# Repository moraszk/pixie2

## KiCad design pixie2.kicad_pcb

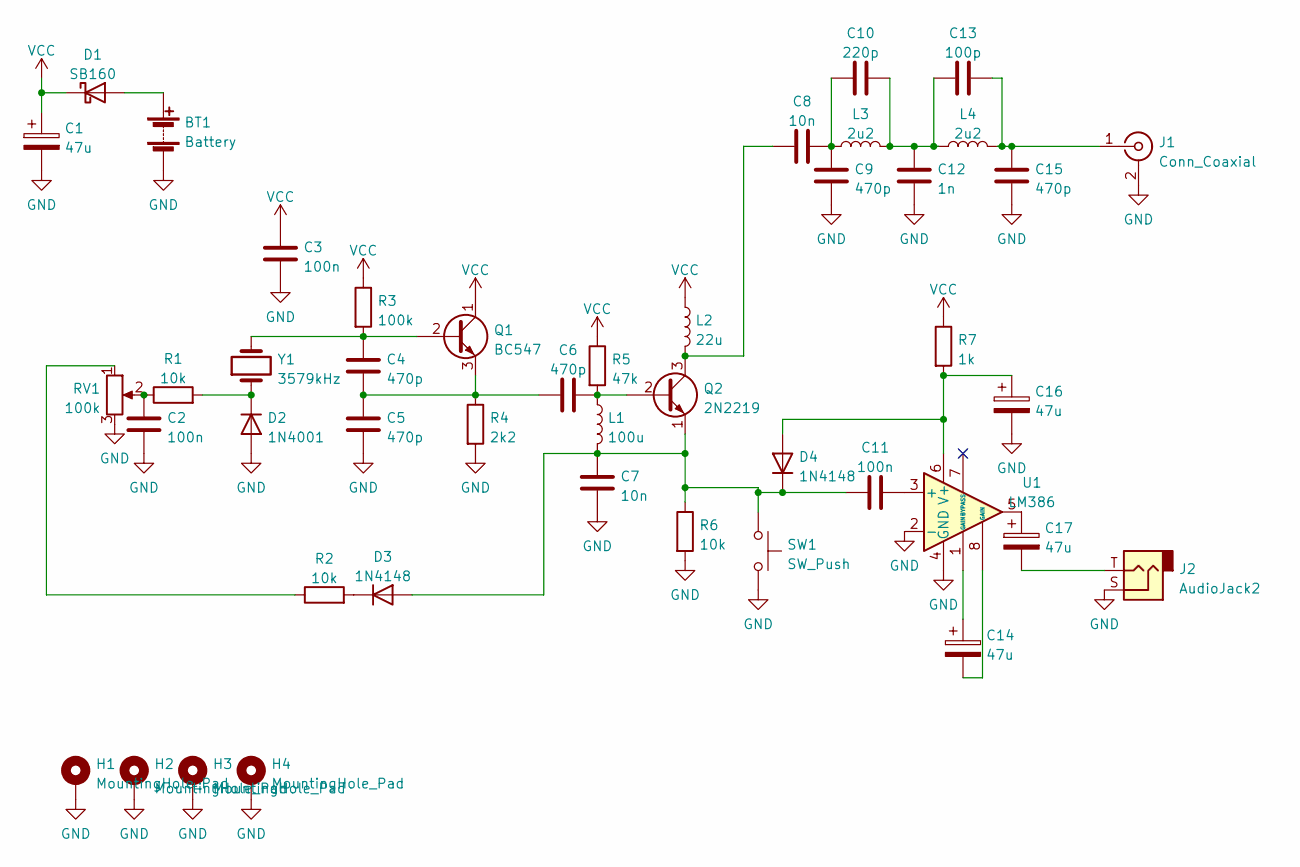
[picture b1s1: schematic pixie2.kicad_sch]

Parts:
BT1: Battery; BarrelJack_GCT_DCJ200-10-A_Horizontal
C1, C14, C16, C17: 47u; CP_Radial_D5.0mm_P2.00mm
C2, C3, C11: 100n; C_Disc_D5.0mm_W2.5mm_P2.50mm
C4, C5, C6, C9, C15: 470p; C_Disc_D3.8mm_W2.6mm_P2.50mm
C7, C8: 10n; C_Disc_D3.8mm_W2.6mm_P2.50mm
C10: 220p; C_Disc_D5.0mm_W2.5mm_P2.50mm
C12: 1n; C_Rect_L4.0mm_W2.5mm_P2.50mm
C13: 100p; C_Disc_D5.0mm_W2.5mm_P2.50mm
D1: SB160; D_DO-41_SOD81_P5.08mm_Vertical_KathodeUp
D2: 1N4001; D_DO-41_SOD81_P5.08mm_Vertical_KathodeUp
D3: 1N4148; D_DO-35_SOD27_P2.54mm_Vertical_KathodeUp
D4: 1N4148; D_DO-35_SOD27_P7.62mm_Horizontal
H1, H2, H3, H4: MountingHole_Pad; MountingHole_3.2mm_M3_Pad
J1: Conn_Coaxial; MountingHole_4.3mm_M4_Pad
J2: AudioJack2; Jack_3.5mm_Ledino_KB3SPRS_Horizontal
L1: 100u; L_Axial_L7.0mm_D3.3mm_P5.08mm_Vertical_Fastron_MICC
L2: 22u; L_Axial_L7.0mm_D3.3mm_P10.16mm_Horizontal_Fastron_MICC
L3: 2u2; L_Axial_L7.0mm_D3.3mm_P10.16mm_Horizontal_Fastron_MICC
L4: 2u2; L_Axial_L7.0mm_D3.3mm_P5.08mm_Vertical_Fastron_MICC
Q1: BC547; TO-92_Inline
Q2: 2N2219; TO-39-3
R1: 10k; R_Axial_DIN0204_L3.6mm_D1.6mm_P2.54mm_Vertical
R2, R6: 10k; R_Axial_DIN0204_L3.6mm_D1.6mm_P5.08mm_Horizontal
R3: 100k; R_Axial_DIN0204_L3.6mm_D1.6mm_P2.54mm_Vertical
R4: 2k2; R_Axial_DIN0204_L3.6mm_D1.6mm_P5.08mm_Horizontal
R5: 47k; R_Axial_DIN0204_L3.6mm_D1.6mm_P5.08mm_Horizontal
R7: 1k; R_Axial_DIN0204_L3.6mm_D1.6mm_P5.08mm_Horizontal
RV1: 100k; Potentiometer_Piher_PT-6-V_Vertical
SW1: SW_Push; SW_PUSH_6mm_H9.5mm
U1: LM386; DIP-8_W7.62mm_LongPads
Y1: 3579kHz; Crystal_HC49-U_Vertical

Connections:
GND: BT1.2 (-), C1.2, C2.2, C3.2, C5.2, C7.2, C9.2, C12.2, C15.2, C16.2, D2.2 (A), H1.1, H2.1, H3.1, H4.1, J1.2 (Ext), J2.S, R4.2, R6.2, RV1.3, SW1.2, U1.2 (-), U1.4 (GND)
unnamed: BT1.1 (+), D1.2 (A)
unnamed: C2.1, R1.1, RV1.2
unnamed: C4.1, Q1.2 (B), R3.2, Y1.2
unnamed: C4.2, C5.1, C6.1, Q1.3 (E), R4.1
unnamed: C6.2, L1.1, Q2.2 (B), R5.2
unnamed: C8.1, L2.2, Q2.3 (C)
unnamed: C8.2, C9.1, C10.1, L3.1
unnamed: C10.2, C12.1, C13.1, L3.2, L4.1
unnamed: C7.1, C11.1, D3.2 (A), D4.1 (K), L1.2, Q2.1 (E), R6.1, SW1.1
unnamed: C11.2, U1.3 (+)
unnamed: C13.2, C15.1, J1.1 (In), L4.2
unnamed: C14.1, U1.1 (GAIN)
unnamed: C14.2, U1.8 (GAIN)
unnamed: C16.1, D4.2 (A), R7.2, U1.6 (V+)
unnamed: C17.1, U1.5
unnamed: C17.2, J2.T
unnamed: D2.1 (K), R1.2, Y1.1
unnamed: D3.1 (K), R2.2
unnamed: R2.1, RV1.1
VCC: C1.1, C3.1, D1.1 (K), L2.1, Q1.1 (C), R3.1, R5.1, R7.1

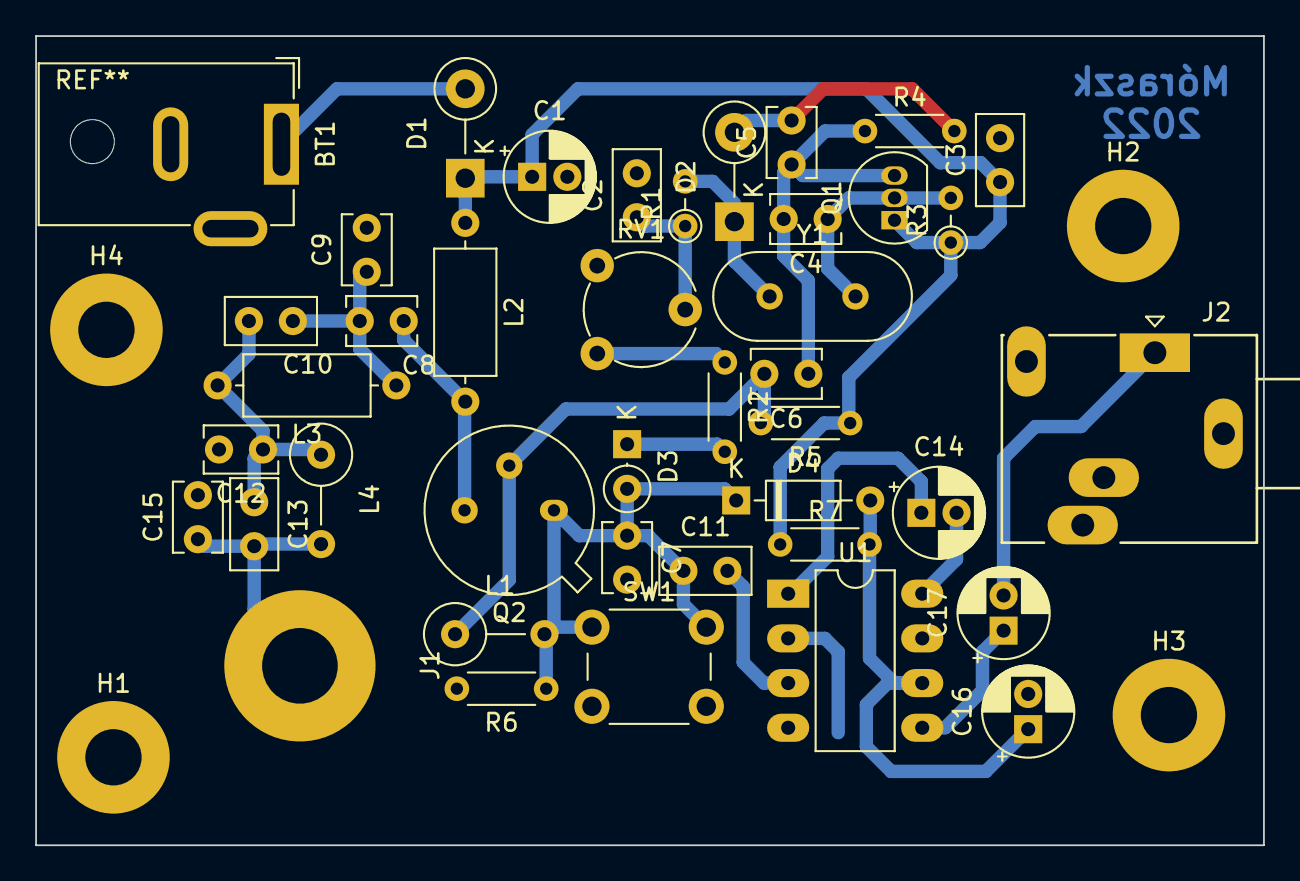
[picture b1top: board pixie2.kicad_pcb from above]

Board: 2 copper layers, 69.8 x 46.0 mm, 45 parts (0 on the bottom side), 21 nets.

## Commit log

2022-11-03 fix vcc line
2022-11-03 Finalize
2022-11-03 Edge.Cuts decrease
